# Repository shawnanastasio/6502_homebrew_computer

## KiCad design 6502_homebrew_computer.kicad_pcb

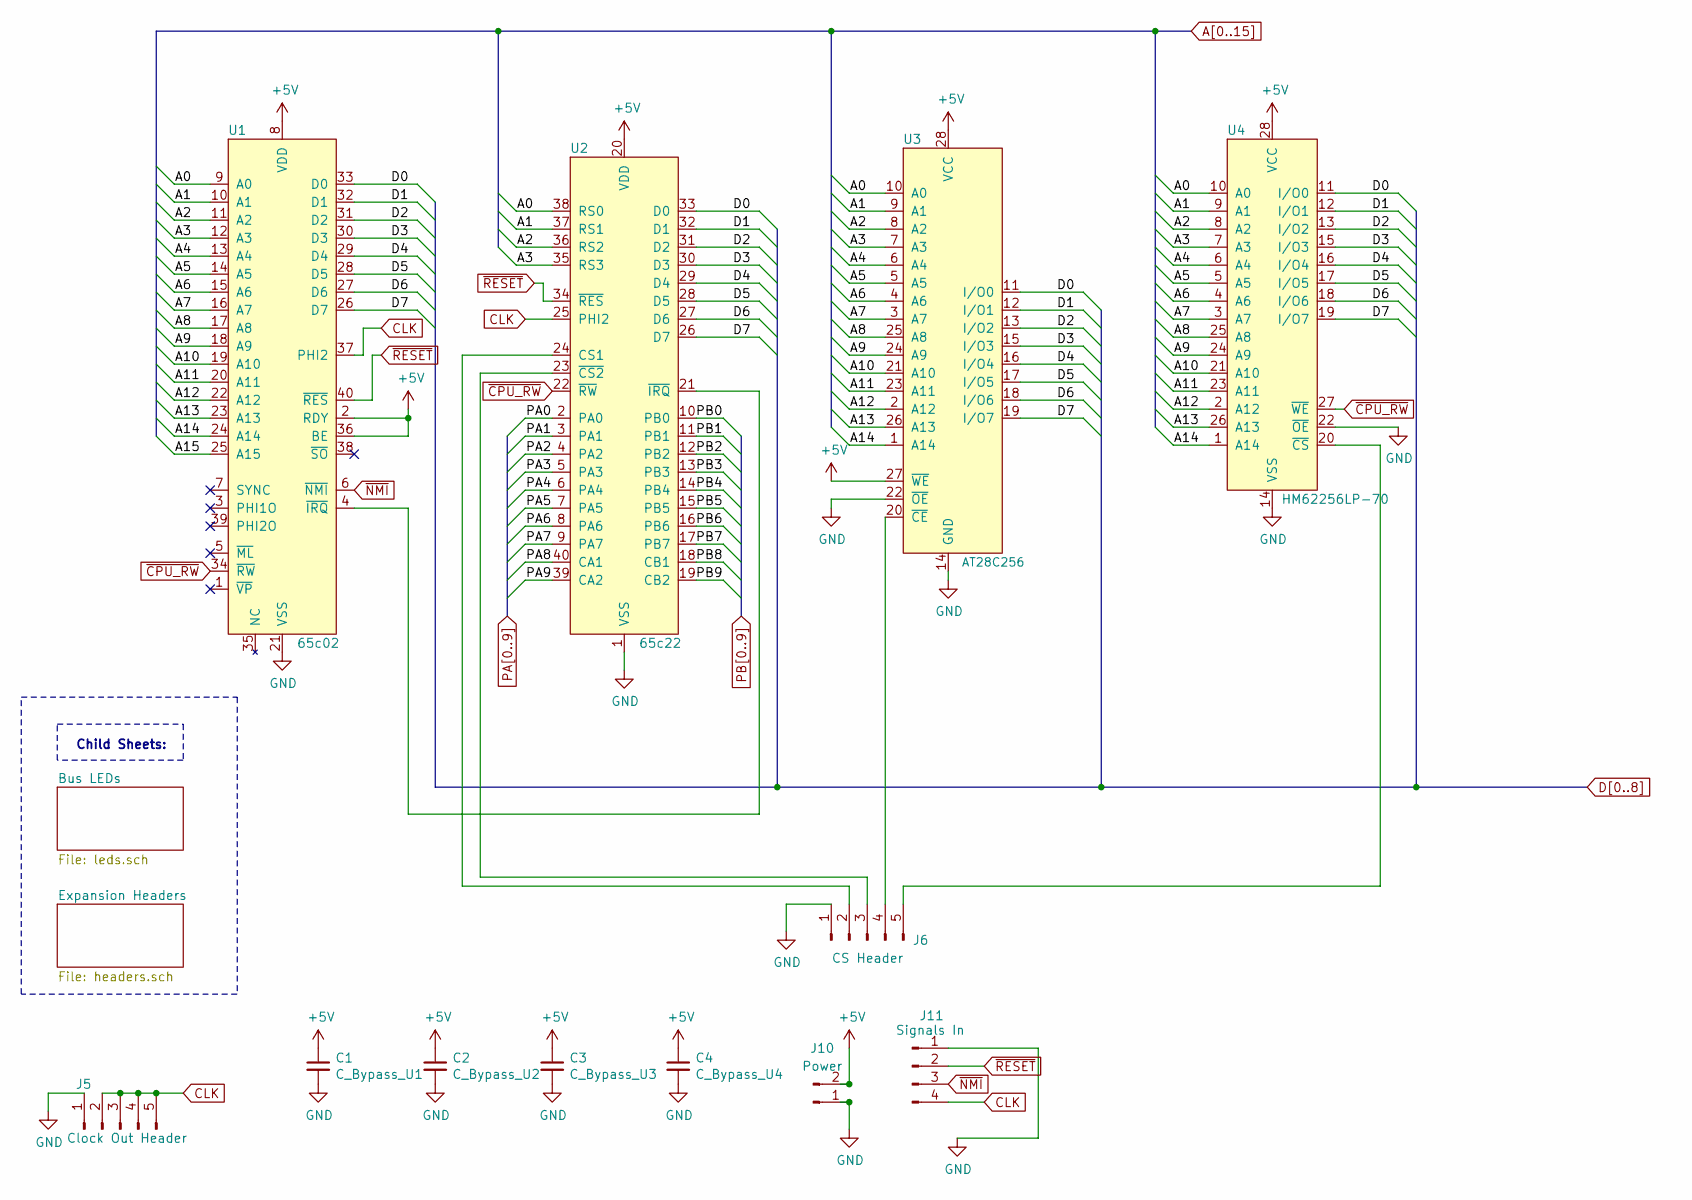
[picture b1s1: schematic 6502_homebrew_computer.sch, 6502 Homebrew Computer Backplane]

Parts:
C1: C_Bypass_U1; C_0805_2012Metric
C2: C_Bypass_U2; C_0805_2012Metric
C3: C_Bypass_U3; C_0805_2012Metric
C4: C_Bypass_U4; C_0805_2012Metric
J5: Clock Out Header; PinHeader_1x05_P2.54mm_Vertical
J6: CS Header; PinHeader_1x05_P2.54mm_Vertical
J10: Power; PinHeader_1x02_P2.54mm_Vertical
J11: Signals In; PinHeader_1x04_P2.54mm_Vertical
U1: 65c02; DIP-40_W15.24mm_Socket
U2: 65c22; DIP-40_W15.24mm_Socket
U3: AT28C256; DIP-28_W15.24mm_Socket
U4: HM62256LP-70; DIP-28_W15.24mm_Socket

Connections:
+5V: C1.1, C2.1, C3.1, C4.1, J10.2, U1.2 (RDY), U1.8 (VDD), U1.36 (BE), U2.20 (VDD), U3.27 (~WE), U3.28 (VCC), U4.28 (VCC); also elsewhere on the board
A0: U1.9 (A0), U2.38 (RS0), U3.10 (A0), U4.10 (A0); also elsewhere on the board
A1: U1.10 (A1), U2.37 (RS1), U3.9 (A1), U4.9 (A1); also elsewhere on the board
A2: U1.11 (A2), U2.36 (RS2), U3.8 (A2), U4.8 (A2); also elsewhere on the board
A3: U1.12 (A3), U2.35 (RS3), U3.7 (A3), U4.7 (A3); also elsewhere on the board
A4: U1.13 (A4), U3.6 (A4), U4.6 (A4); also elsewhere on the board
A5: U1.14 (A5), U3.5 (A5), U4.5 (A5); also elsewhere on the board
A6: U1.15 (A6), U3.4 (A6), U4.4 (A6); also elsewhere on the board
A7: U1.16 (A7), U3.3 (A7), U4.3 (A7); also elsewhere on the board
A8: U1.17 (A8), U3.25 (A8), U4.25 (A8); also elsewhere on the board
A9: U1.18 (A9), U3.24 (A9), U4.24 (A9); also elsewhere on the board
A10: U1.19 (A10), U3.21 (A10), U4.21 (A10); also elsewhere on the board
A11: U1.20 (A11), U3.23 (A11), U4.23 (A11); also elsewhere on the board
A12: U1.22 (A12), U3.2 (A12), U4.2 (A12); also elsewhere on the board
A13: U1.23 (A13), U3.26 (A13), U4.26 (A13); also elsewhere on the board
A14: U1.24 (A14), U3.1 (A14), U4.1 (A14); also elsewhere on the board
A15: U1.25 (A15); also elsewhere on the board
CLK: J5.2, J5.3, J5.4, J5.5, J11.4, U1.37 (PHI2), U2.25 (PHI2)
D0: U1.33 (D0), U2.33 (D0), U3.11 (I/O0), U4.11 (I/O0); also elsewhere on the board
D1: U1.32 (D1), U2.32 (D1), U3.12 (I/O1), U4.12 (I/O1); also elsewhere on the board
D2: U1.31 (D2), U2.31 (D2), U3.13 (I/O2), U4.13 (I/O2); also elsewhere on the board
D3: U1.30 (D3), U2.30 (D3), U3.15 (I/O3), U4.15 (I/O3); also elsewhere on the board
D4: U1.29 (D4), U2.29 (D4), U3.16 (I/O4), U4.16 (I/O4); also elsewhere on the board
D5: U1.28 (D5), U2.28 (D5), U3.17 (I/O5), U4.17 (I/O5); also elsewhere on the board
D6: U1.27 (D6), U2.27 (D6), U3.18 (I/O6), U4.18 (I/O6); also elsewhere on the board
D7: U1.26 (D7), U2.26 (D7), U3.19 (I/O7), U4.19 (I/O7); also elsewhere on the board
GND: C1.2, C2.2, C3.2, C4.2, J5.1, J6.1, J10.1, J11.1, U1.21 (VSS), U2.1 (VSS), U3.14 (GND), U3.22 (~OE), U4.14 (VSS), U4.22 (~OE); also elsewhere on the board
unnamed: J6.2, U2.24 (CS1)
unnamed: J6.3, U2.23 (~CS2)
unnamed: J6.4, U3.20 (~CE)
unnamed: J6.5, U4.20 (~CS)
unnamed: U1.4 (~IRQ), U2.21 (~IRQ)
PA0: U2.2 (PA0); also elsewhere on the board
PA1: U2.3 (PA1); also elsewhere on the board
PA2: U2.4 (PA2); also elsewhere on the board
PA3: U2.5 (PA3); also elsewhere on the board
PA4: U2.6 (PA4); also elsewhere on the board
PA5: U2.7 (PA5); also elsewhere on the board
PA6: U2.8 (PA6); also elsewhere on the board
PA7: U2.9 (PA7); also elsewhere on the board
PA8: U2.40 (CA1); also elsewhere on the board
PA9: U2.39 (CA2); also elsewhere on the board
PB0: U2.10 (PB0); also elsewhere on the board
PB1: U2.11 (PB1); also elsewhere on the board
PB2: U2.12 (PB2); also elsewhere on the board
PB3: U2.13 (PB3); also elsewhere on the board
PB4: U2.14 (PB4); also elsewhere on the board
PB5: U2.15 (PB5); also elsewhere on the board
PB6: U2.16 (PB6); also elsewhere on the board
PB7: U2.17 (PB7); also elsewhere on the board
PB8: U2.18 (CB1); also elsewhere on the board
PB9: U2.19 (CB2); also elsewhere on the board
~CPU_RW: U1.34 (~RW), U2.22 (~RW), U4.27 (~WE)
~NMI: J11.3, U1.6 (~NMI)
~RESET: J11.2, U1.40 (~RES), U2.34 (~RES)

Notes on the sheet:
Child Sheets:

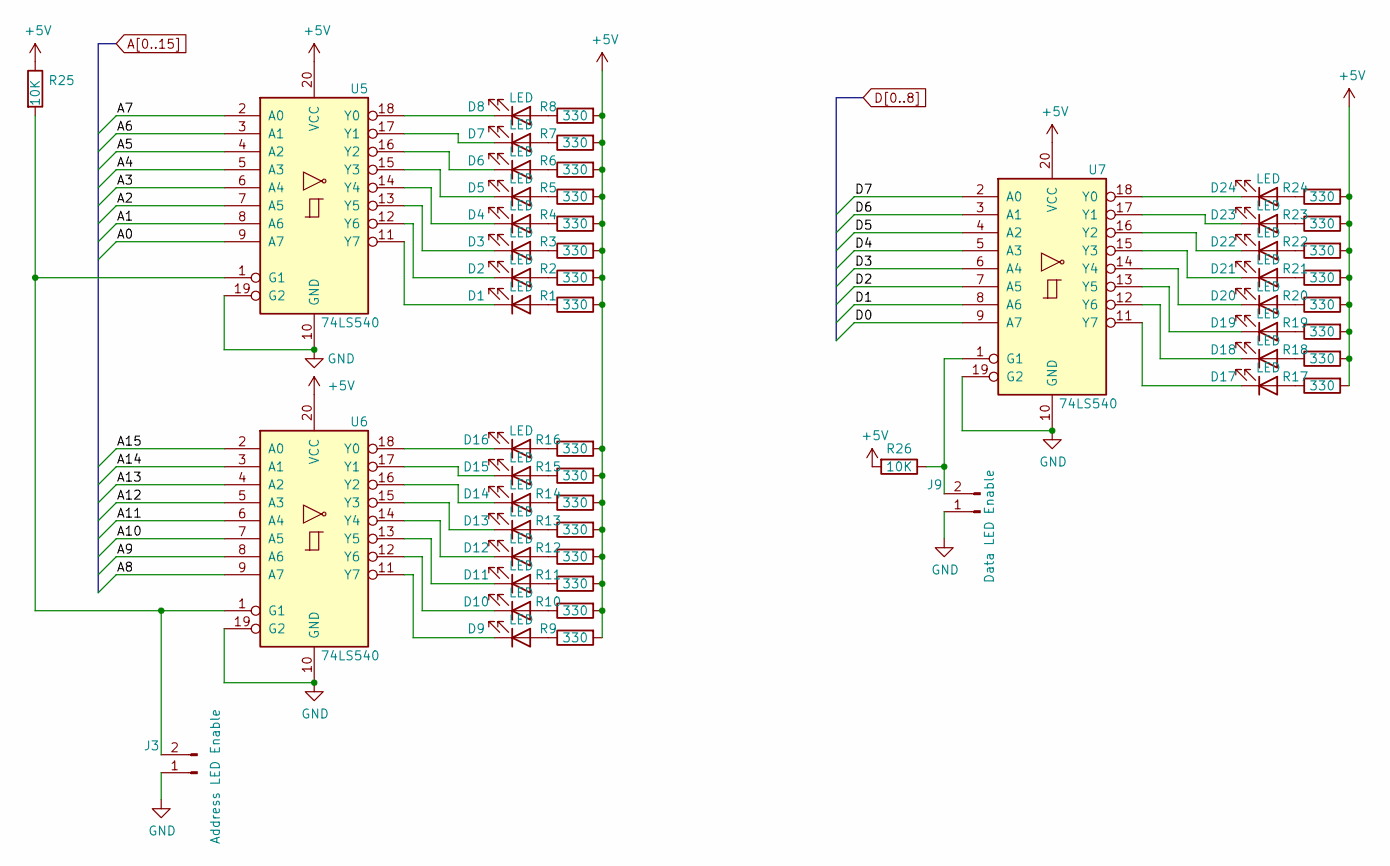
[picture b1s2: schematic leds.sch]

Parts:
D1, D2, D3, D4, D5, D6, D7, D8, D9, D10, D11, D12, D13, D14, D15, D16, D17, D18, D19, D20, D21, D22, D23, D24: LED; LED_0805_2012Metric
J3: Address LED Enable; PinHeader_1x02_P2.54mm_Vertical
J9: Data LED Enable; PinHeader_1x02_P2.54mm_Vertical
R1, R2, R3, R4, R5, R6, R7, R8, R9, R10, R11, R12, R13, R14, R15, R16, R17, R18, R19, R20, R21, R22, R23, R24: 330; R_0805_2012Metric
R25, R26: 10K; R_0805_2012Metric
U5, U6, U7: 74LS540; DIP-20_W7.62mm_Socket

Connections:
+5V: R1.2, R2.2, R3.2, R4.2, R5.2, R6.2, R7.2, R8.2, R9.2, R10.2, R11.2, R12.2, R13.2, R14.2, R15.2, R16.2, R17.2, R18.2, R19.2, R20.2, R21.2, R22.2, R23.2, R24.2, R25.1, R26.2, U5.20 (VCC), U6.20 (VCC), U7.20 (VCC); also elsewhere on the board
A0: U5.9 (A7); also elsewhere on the board
A1: U5.8 (A6); also elsewhere on the board
A2: U5.7 (A5); also elsewhere on the board
A3: U5.6 (A4); also elsewhere on the board
A4: U5.5 (A3); also elsewhere on the board
A5: U5.4 (A2); also elsewhere on the board
A6: U5.3 (A1); also elsewhere on the board
A7: U5.2 (A0); also elsewhere on the board
A8: U6.9 (A7); also elsewhere on the board
A9: U6.8 (A6); also elsewhere on the board
A10: U6.7 (A5); also elsewhere on the board
A11: U6.6 (A4); also elsewhere on the board
A12: U6.5 (A3); also elsewhere on the board
A13: U6.4 (A2); also elsewhere on the board
A14: U6.3 (A1); also elsewhere on the board
A15: U6.2 (A0); also elsewhere on the board
D0: U7.9 (A7); also elsewhere on the board
D1: U7.8 (A6); also elsewhere on the board
D2: U7.7 (A5); also elsewhere on the board
D3: U7.6 (A4); also elsewhere on the board
D4: U7.5 (A3); also elsewhere on the board
D5: U7.4 (A2); also elsewhere on the board
D6: U7.3 (A1); also elsewhere on the board
D7: U7.2 (A0); also elsewhere on the board
GND: J3.1, J9.1, U5.10 (GND), U5.19 (G2), U6.10 (GND), U6.19 (G2), U7.10 (GND), U7.19 (G2); also elsewhere on the board
unnamed: D1.1 (K), U5.11 (Y7)
unnamed: D1.2 (A), R1.1
unnamed: D2.1 (K), U5.12 (Y6)
unnamed: D2.2 (A), R2.1
unnamed: D3.1 (K), U5.13 (Y5)
unnamed: D3.2 (A), R3.1
unnamed: D4.1 (K), U5.14 (Y4)
unnamed: D4.2 (A), R4.1
unnamed: D5.1 (K), U5.15 (Y3)
unnamed: D5.2 (A), R5.1
unnamed: D6.1 (K), U5.16 (Y2)
unnamed: D6.2 (A), R6.1
unnamed: D7.1 (K), U5.17 (Y1)
unnamed: D7.2 (A), R7.1
unnamed: D8.1 (K), U5.18 (Y0)
unnamed: D8.2 (A), R8.1
unnamed: D9.1 (K), U6.11 (Y7)
unnamed: D9.2 (A), R9.1
unnamed: D10.1 (K), U6.12 (Y6)
unnamed: D10.2 (A), R10.1
unnamed: D11.1 (K), U6.13 (Y5)
unnamed: D11.2 (A), R11.1
unnamed: D12.1 (K), U6.14 (Y4)
unnamed: D12.2 (A), R12.1
unnamed: D13.1 (K), U6.15 (Y3)
unnamed: D13.2 (A), R13.1
unnamed: D14.1 (K), U6.16 (Y2)
unnamed: D14.2 (A), R14.1
unnamed: D15.1 (K), U6.17 (Y1)
unnamed: D15.2 (A), R15.1
unnamed: D16.1 (K), U6.18 (Y0)
unnamed: D16.2 (A), R16.1
unnamed: D17.1 (K), U7.11 (Y7)
unnamed: D17.2 (A), R17.1
unnamed: D18.1 (K), U7.12 (Y6)
unnamed: D18.2 (A), R18.1
unnamed: D19.1 (K), U7.13 (Y5)
unnamed: D19.2 (A), R19.1
unnamed: D20.1 (K), U7.14 (Y4)
unnamed: D20.2 (A), R20.1
unnamed: D21.1 (K), U7.15 (Y3)
unnamed: D21.2 (A), R21.1
unnamed: D22.1 (K), U7.16 (Y2)
unnamed: D22.2 (A), R22.1
unnamed: D23.1 (K), U7.17 (Y1)
unnamed: D23.2 (A), R23.1
unnamed: D24.1 (K), U7.18 (Y0)
unnamed: D24.2 (A), R24.1
unnamed: J3.2, R25.2, U5.1 (G1), U6.1 (G1)
unnamed: J9.2, R26.1, U7.1 (G1)

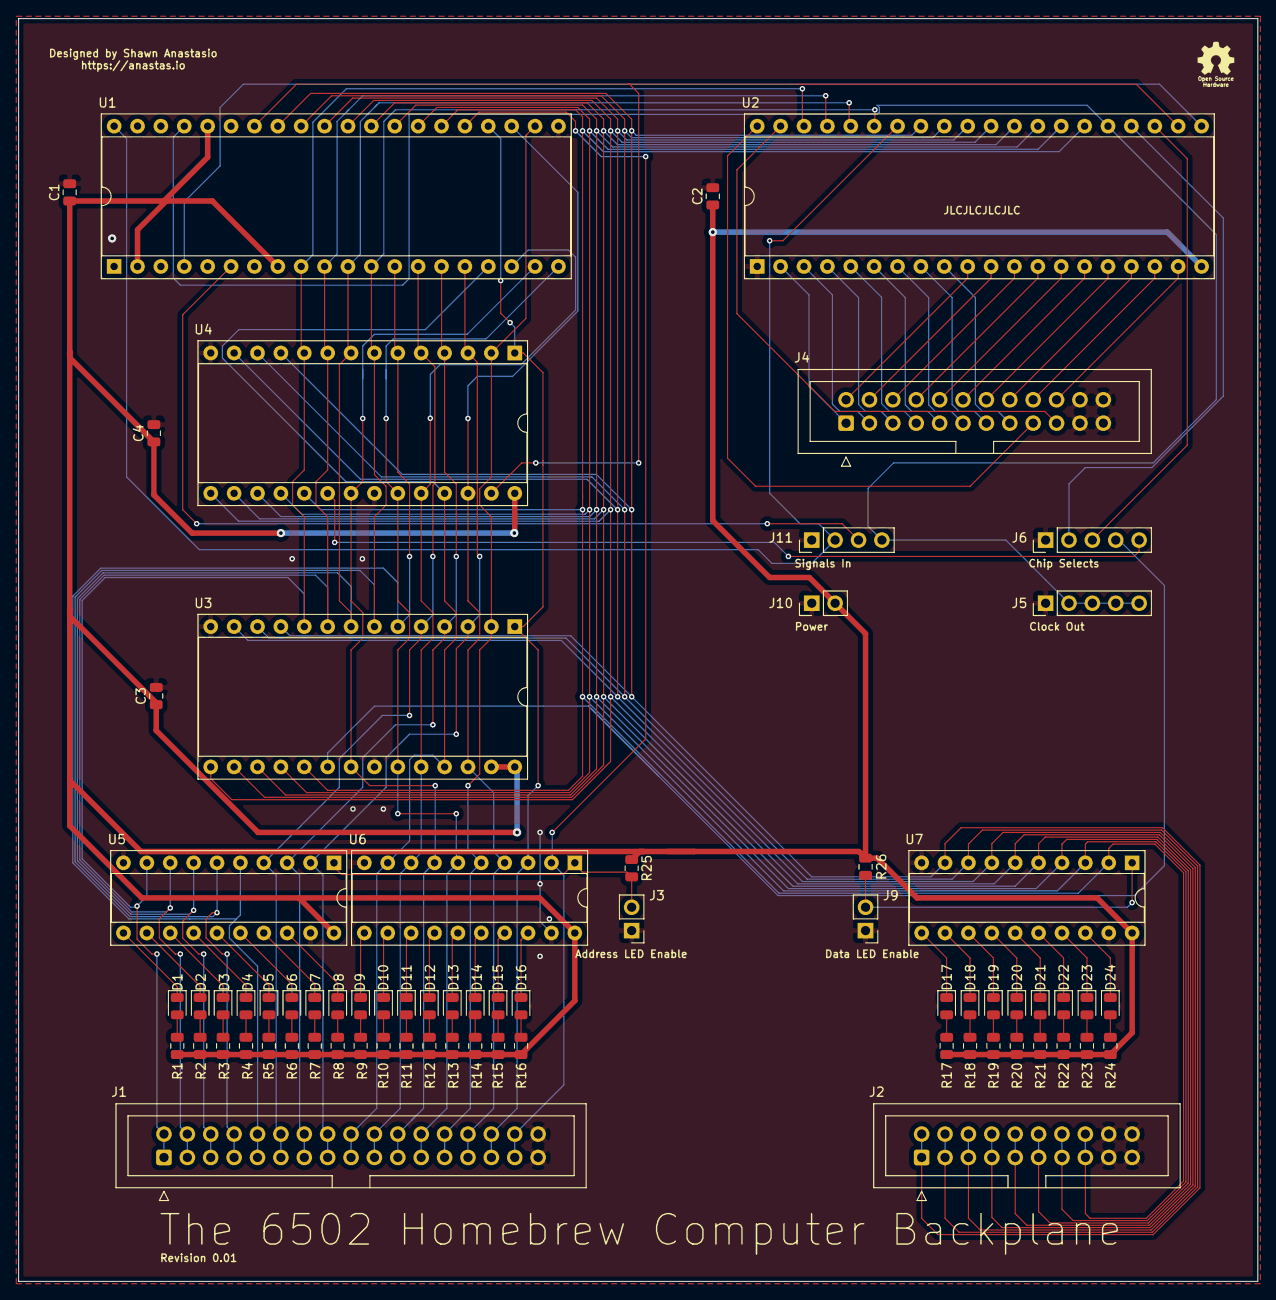
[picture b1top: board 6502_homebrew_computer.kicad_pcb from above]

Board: 2 copper layers, 134.6 x 137.2 mm, 70 parts (0 on the bottom side), 105 nets.

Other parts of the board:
J1: Address Bus Header; IDC-Header_2x17_P2.54mm_Vertical
J2: Data Bus Header; IDC-Header_2x10_P2.54mm_Vertical
J4: Conn_02x12_Odd_Even; IDC-Header_2x12_P2.54mm_Vertical

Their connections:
A0: J1.1, J1.2; also elsewhere on the board
A1: J1.3, J1.4; also elsewhere on the board
A2: J1.5, J1.6; also elsewhere on the board
A3: J1.7, J1.8; also elsewhere on the board
A4: J1.9, J1.10; also elsewhere on the board
A5: J1.11, J1.12; also elsewhere on the board
A6: J1.13, J1.14; also elsewhere on the board
A7: J1.15, J1.16; also elsewhere on the board
A8: J1.17, J1.18; also elsewhere on the board
A9: J1.19, J1.20; also elsewhere on the board
A10: J1.21, J1.22; also elsewhere on the board
A11: J1.23, J1.24; also elsewhere on the board
A12: J1.25, J1.26; also elsewhere on the board
A13: J1.27, J1.28; also elsewhere on the board
A14: J1.29, J1.30; also elsewhere on the board
A15: J1.31, J1.32; also elsewhere on the board
D0: J2.1, J2.2; also elsewhere on the board
D1: J2.3, J2.4; also elsewhere on the board
D2: J2.5, J2.6; also elsewhere on the board
D3: J2.7, J2.8; also elsewhere on the board
D4: J2.9, J2.10; also elsewhere on the board
D5: J2.11, J2.12; also elsewhere on the board
D6: J2.13, J2.14; also elsewhere on the board
D7: J2.15, J2.16; also elsewhere on the board
GND: J1.33, J1.34, J2.17, J2.18, J2.19, J2.20, J4.21, J4.22, J4.23, J4.24; also elsewhere on the board
PA0: J4.1; also elsewhere on the board
PA1: J4.3; also elsewhere on the board
PA2: J4.5; also elsewhere on the board
PA3: J4.7; also elsewhere on the board
PA4: J4.9; also elsewhere on the board
PA5: J4.11; also elsewhere on the board
PA6: J4.13; also elsewhere on the board
PA7: J4.15; also elsewhere on the board
PA8: J4.17; also elsewhere on the board
PA9: J4.19; also elsewhere on the board
PB0: J4.2; also elsewhere on the board
PB1: J4.4; also elsewhere on the board
PB2: J4.6; also elsewhere on the board
PB3: J4.8; also elsewhere on the board
PB4: J4.10; also elsewhere on the board
PB5: J4.12; also elsewhere on the board
PB6: J4.14; also elsewhere on the board
PB7: J4.16; also elsewhere on the board
PB8: J4.18; also elsewhere on the board
PB9: J4.20; also elsewhere on the board

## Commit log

2020-08-15 Initial commit - 0.01
